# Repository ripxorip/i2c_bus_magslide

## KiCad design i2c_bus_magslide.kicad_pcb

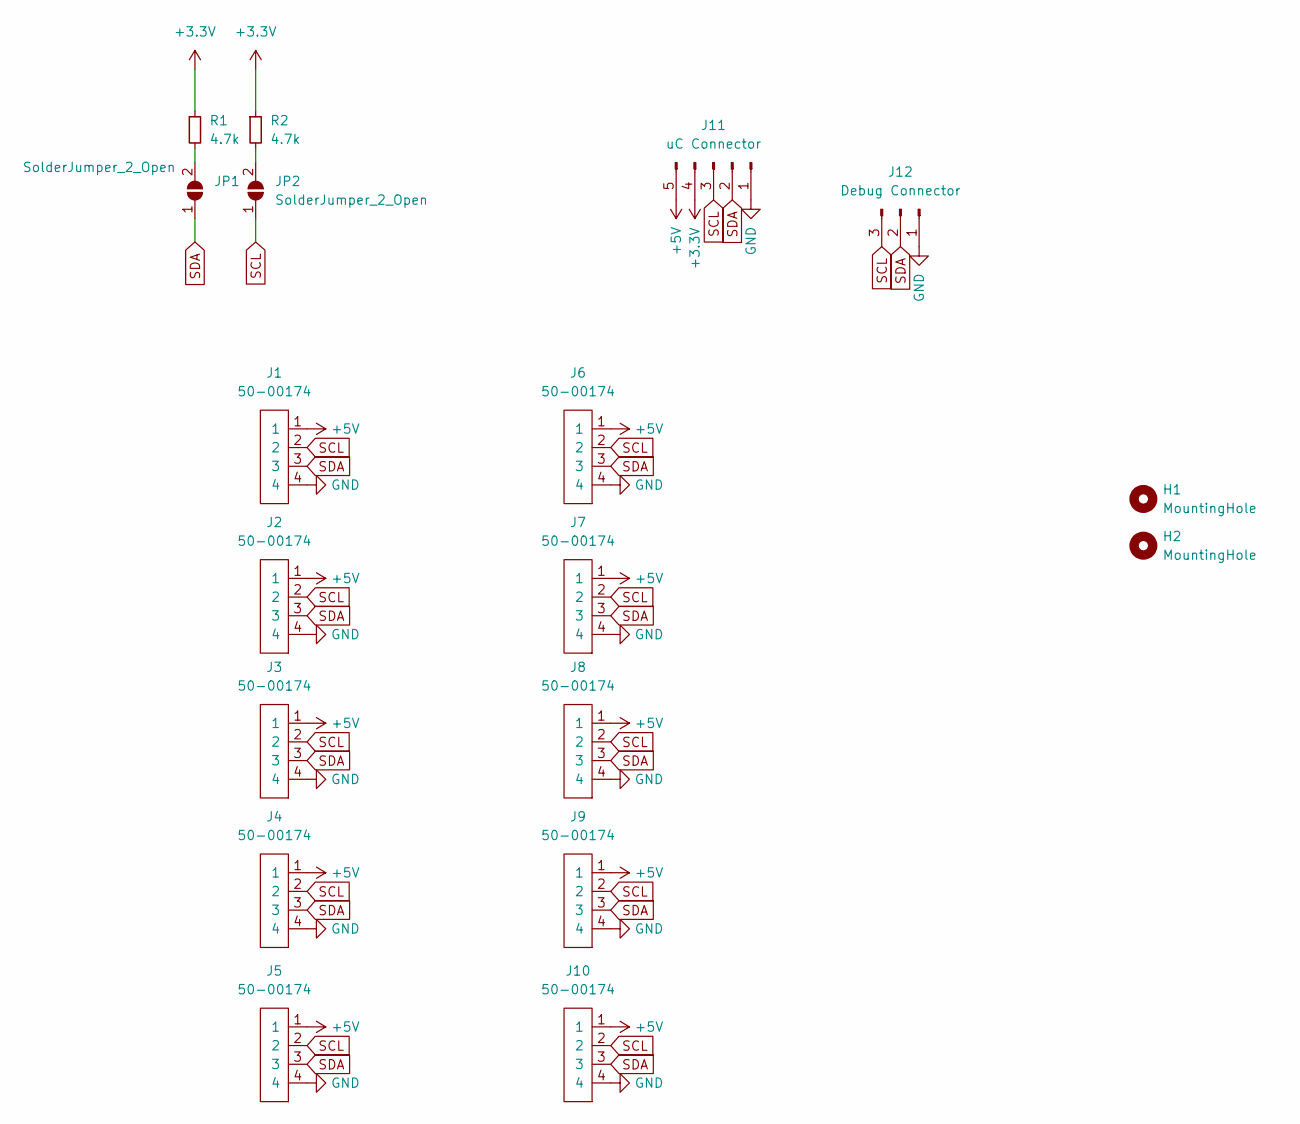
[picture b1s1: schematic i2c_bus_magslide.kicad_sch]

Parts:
H1, H2: MountingHole; MountingHole_3.2mm_M3
J1, J2, J3, J4, J5, J6, J7, J8, J9, J10: 50-00174; 54-00174
J11: uC Connector; PinHeader_1x05_P2.54mm_Vertical
J12: Debug Connector; PinHeader_1x03_P2.54mm_Vertical
JP1, JP2: SolderJumper_2_Open; SolderJumper-2_P1.3mm_Open_RoundedPad1.0x1.5mm
R1, R2: 4.7k; R_Box_L8.4mm_W2.5mm_P5.08mm

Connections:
+3V3: J11.4, R1.1, R2.1
+5V: J1.1, J2.1, J3.1, J4.1, J5.1, J6.1, J7.1, J8.1, J9.1, J10.1, J11.5
GND: J1.4, J2.4, J3.4, J4.4, J5.4, J6.4, J7.4, J8.4, J9.4, J10.4, J11.1, J12.1
unnamed: JP1.2 (B), R1.2
unnamed: JP2.2 (B), R2.2
SCL: J1.2, J2.2, J3.2, J4.2, J5.2, J6.2, J7.2, J8.2, J9.2, J10.2, J11.3, J12.3, JP2.1 (A)
SDA: J1.3, J2.3, J3.3, J4.3, J5.3, J6.3, J7.3, J8.3, J9.3, J10.3, J11.2, J12.2, JP1.1 (A)

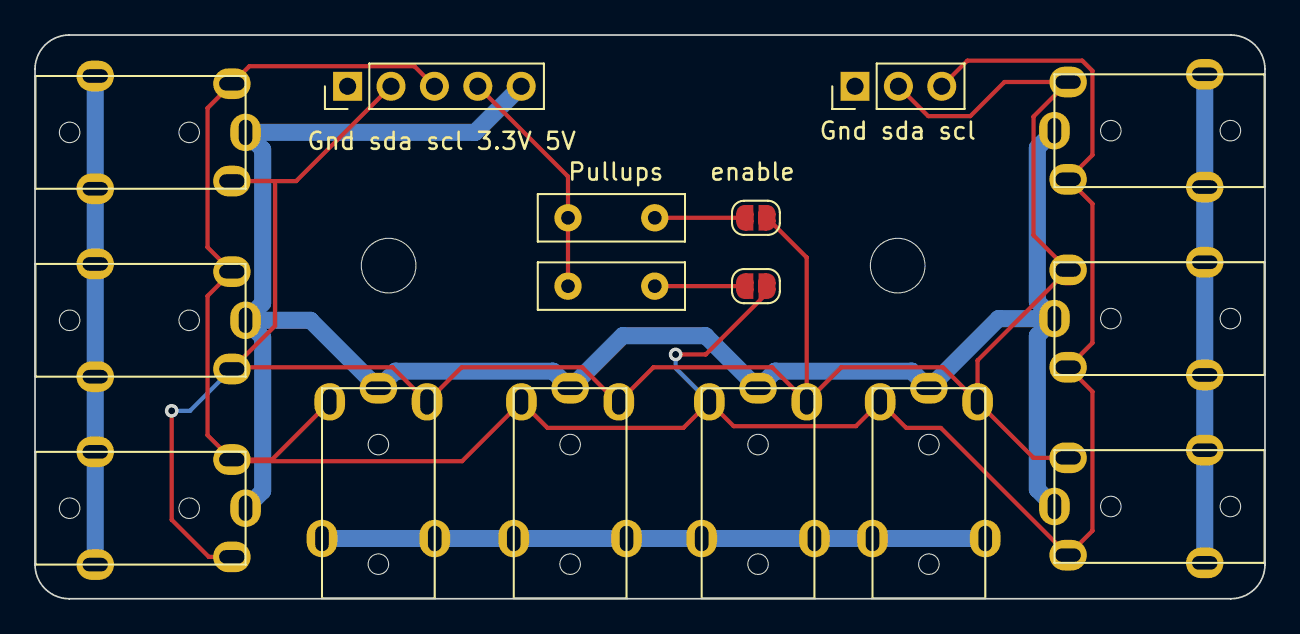
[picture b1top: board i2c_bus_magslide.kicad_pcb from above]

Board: 2 copper layers, 72.0 x 33.0 mm, 18 parts (0 on the bottom side), 7 nets.

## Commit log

2022-05-17 Adds schematics
